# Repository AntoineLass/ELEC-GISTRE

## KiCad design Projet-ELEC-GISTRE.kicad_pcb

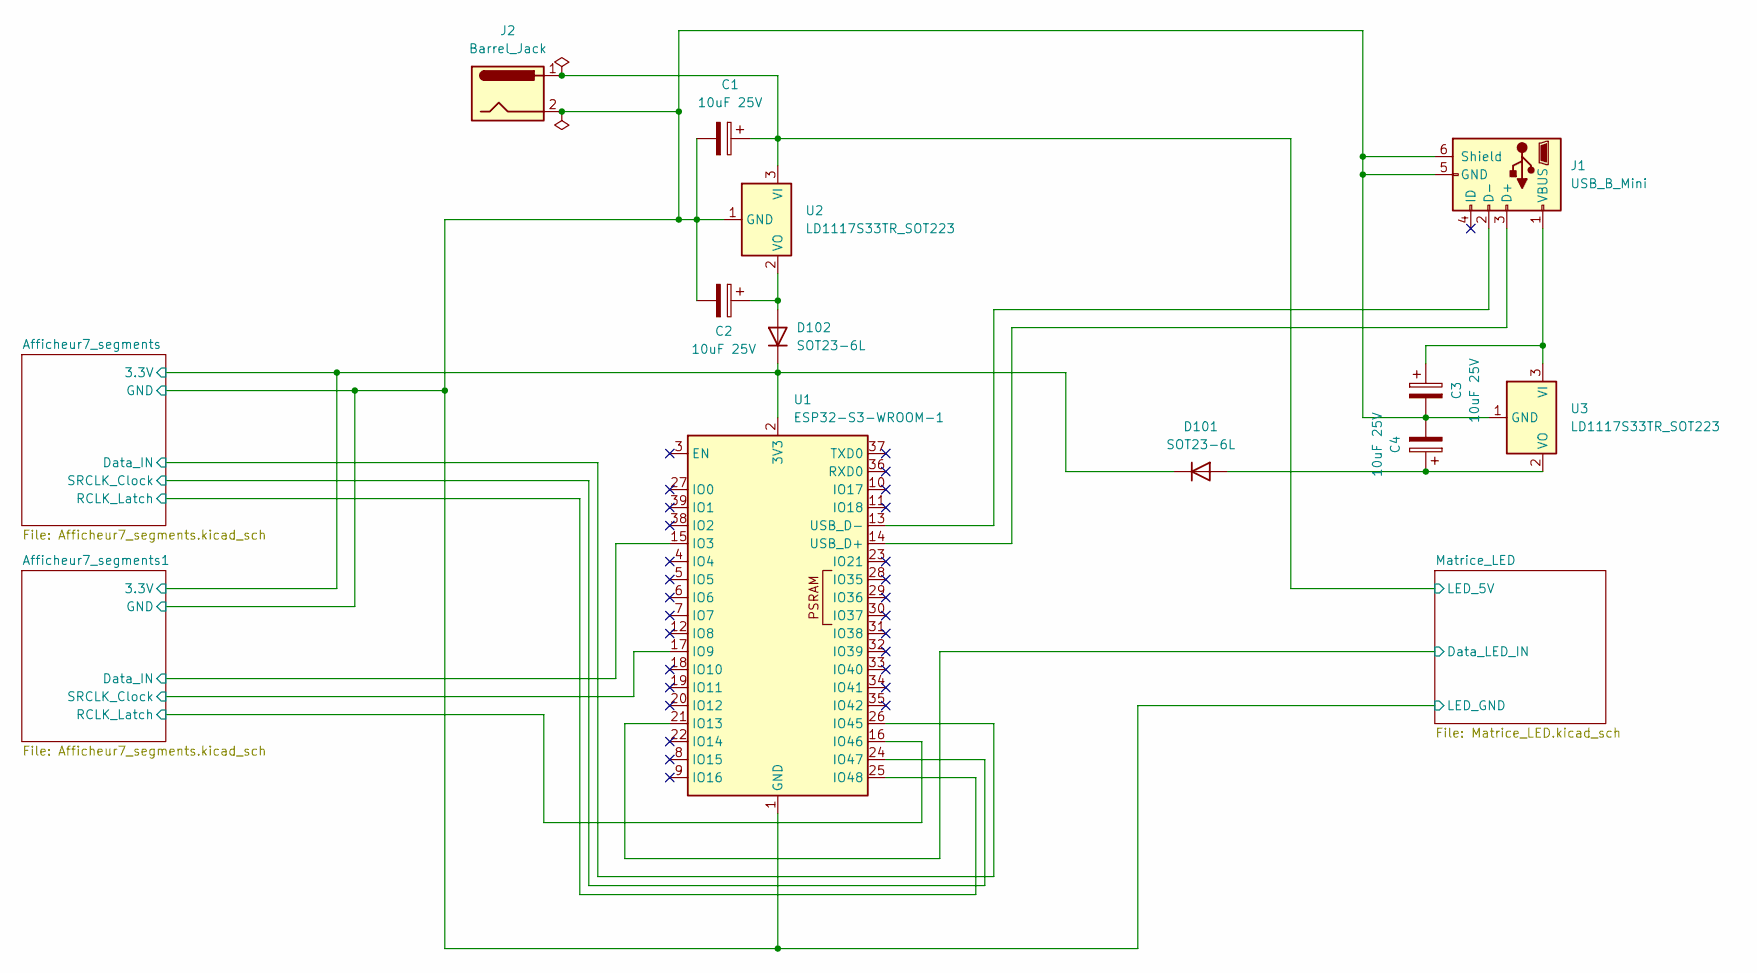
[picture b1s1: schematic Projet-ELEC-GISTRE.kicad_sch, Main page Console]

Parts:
C1, C2, C3, C4: 10uF 25V; C_0603_1608Metric_Pad1.08x0.95mm_HandSolder
D101, D102: SOT23-6L; TSOT-23-6_HandSoldering
J1: USB_B_Mini; USB_Mini-B_Wuerth_65100516121_Horizontal
J2: Barrel_Jack; BarrelJack_Wuerth_6941xx301002
U1: ESP32-S3-WROOM-1
U2, U3: LD1117S33TR_SOT223; SOT-223-3_TabPin2

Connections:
/Afficheur7_segments1/Data_IN: U1.15 (IO3); also elsewhere on the board
/Afficheur7_segments1/RCLK_Latch: U1.16 (IO46); also elsewhere on the board
/Afficheur7_segments1/SRCLK_Clock: U1.17 (IO9); also elsewhere on the board
/Afficheur7_segments/3.3V: D101.1 (K), D102.1 (K), U1.2 (3V3); also elsewhere on the board
/Afficheur7_segments/Data_IN: U1.26 (IO45); also elsewhere on the board
/Afficheur7_segments/GND: C1.2, C2.2, C3.2, C4.2, J1.5 (GND), J1.6 (Shield), J2.2, U1.1 (GND), U1.40 (GND), U1.41 (GND), U2.1 (GND), U3.1 (GND); also elsewhere on the board
/Afficheur7_segments/RCLK_Latch: U1.25 (IO48); also elsewhere on the board
/Afficheur7_segments/SRCLK_Clock: U1.24 (IO47); also elsewhere on the board
/Matrice_LED/Data_LED_IN: U1.21 (IO13); also elsewhere on the board
/Matrice_LED/LED_5V: C1.1, J2.1, U2.3 (VI); also elsewhere on the board
unnamed: C4.1, D101.2 (A), U3.2 (VO)
unnamed: C2.1, D102.2 (A), U2.2 (VO)
unnamed: J1.3 (D+), U1.14 (USB_D+)
unnamed: J1.2 (D-), U1.13 (USB_D-)
unnamed: C3.1, J1.1 (VBUS), U3.3 (VI)

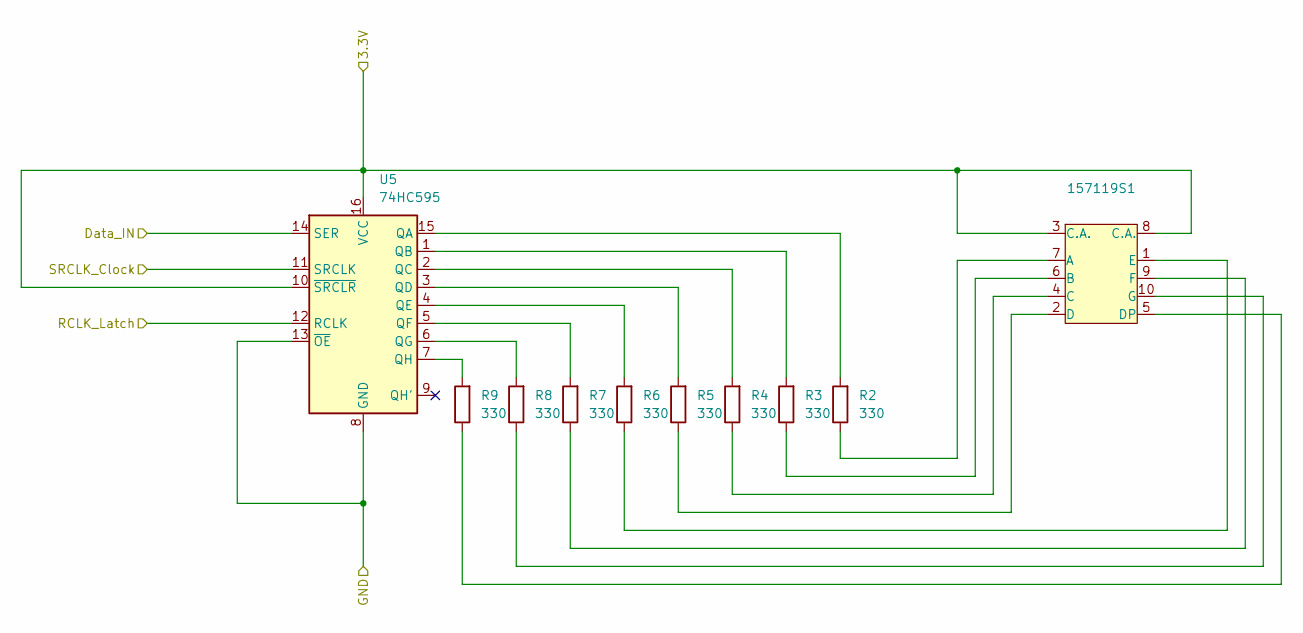
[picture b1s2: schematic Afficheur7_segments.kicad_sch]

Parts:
157119S1: 157119S12801
R2, R3, R4, R5, R6, R7, R8, R9: 330; R_0603_1608Metric_Pad0.98x0.95mm_HandSolder
U5: 74HC595; DIP-16_W7.62mm

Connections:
/Afficheur7_segments/3.3V: 157119S1.3 (C.A.), 157119S1.8 (C.A.), U5.10 (~SRCLR), U5.16 (VCC); also elsewhere on the board
/Afficheur7_segments/Data_IN: U5.14 (SER); also elsewhere on the board
/Afficheur7_segments/GND: U5.8 (GND), U5.13 (~OE); also elsewhere on the board
/Afficheur7_segments/RCLK_Latch: U5.12 (RCLK); also elsewhere on the board
/Afficheur7_segments/SRCLK_Clock: U5.11 (SRCLK); also elsewhere on the board
unnamed: 157119S1.7 (A), R2.1
unnamed: 157119S1.6 (B), R3.1
unnamed: 157119S1.4 (C), R4.1
unnamed: 157119S1.2 (D), R5.1
unnamed: 157119S1.5 (DP), R9.1
unnamed: 157119S1.1 (E), R6.1
unnamed: 157119S1.9 (F), R7.1
unnamed: 157119S1.10 (G), R8.1
unnamed: R2.2, U5.15 (QA)
unnamed: R3.2, U5.1 (QB)
unnamed: R4.2, U5.2 (QC)
unnamed: R5.2, U5.3 (QD)
unnamed: R6.2, U5.4 (QE)
unnamed: R7.2, U5.5 (QF)
unnamed: R8.2, U5.6 (QG)
unnamed: R9.2, U5.7 (QH)

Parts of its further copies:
157119S2: 157119S12801
R10, R11, R12, R13, R14, R15, R16, R17: 330; R_0603_1608Metric_Pad0.98x0.95mm_HandSolder
U4: 74HC595; DIP-16_W7.62mm

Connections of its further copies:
/Afficheur7_segments1/Data_IN: U4.14 (SER); also elsewhere on the board
/Afficheur7_segments1/RCLK_Latch: U4.12 (RCLK); also elsewhere on the board
/Afficheur7_segments1/SRCLK_Clock: U4.11 (SRCLK); also elsewhere on the board
/Afficheur7_segments/3.3V: 157119S2.3 (C.A.), 157119S2.8 (C.A.), U4.10 (~SRCLR), U4.16 (VCC); also elsewhere on the board
/Afficheur7_segments/GND: U4.8 (GND), U4.13 (~OE); also elsewhere on the board
unnamed: 157119S2.7 (A), R17.1
unnamed: 157119S2.6 (B), R16.1
unnamed: 157119S2.4 (C), R15.1
unnamed: 157119S2.2 (D), R14.1
unnamed: 157119S2.5 (DP), R10.1
unnamed: 157119S2.1 (E), R13.1
unnamed: 157119S2.9 (F), R12.1
unnamed: 157119S2.10 (G), R11.1
unnamed: R17.2, U4.15 (QA)
unnamed: R16.2, U4.1 (QB)
unnamed: R15.2, U4.2 (QC)
unnamed: R14.2, U4.3 (QD)
unnamed: R13.2, U4.4 (QE)
unnamed: R12.2, U4.5 (QF)
unnamed: R11.2, U4.6 (QG)
unnamed: R10.2, U4.7 (QH)

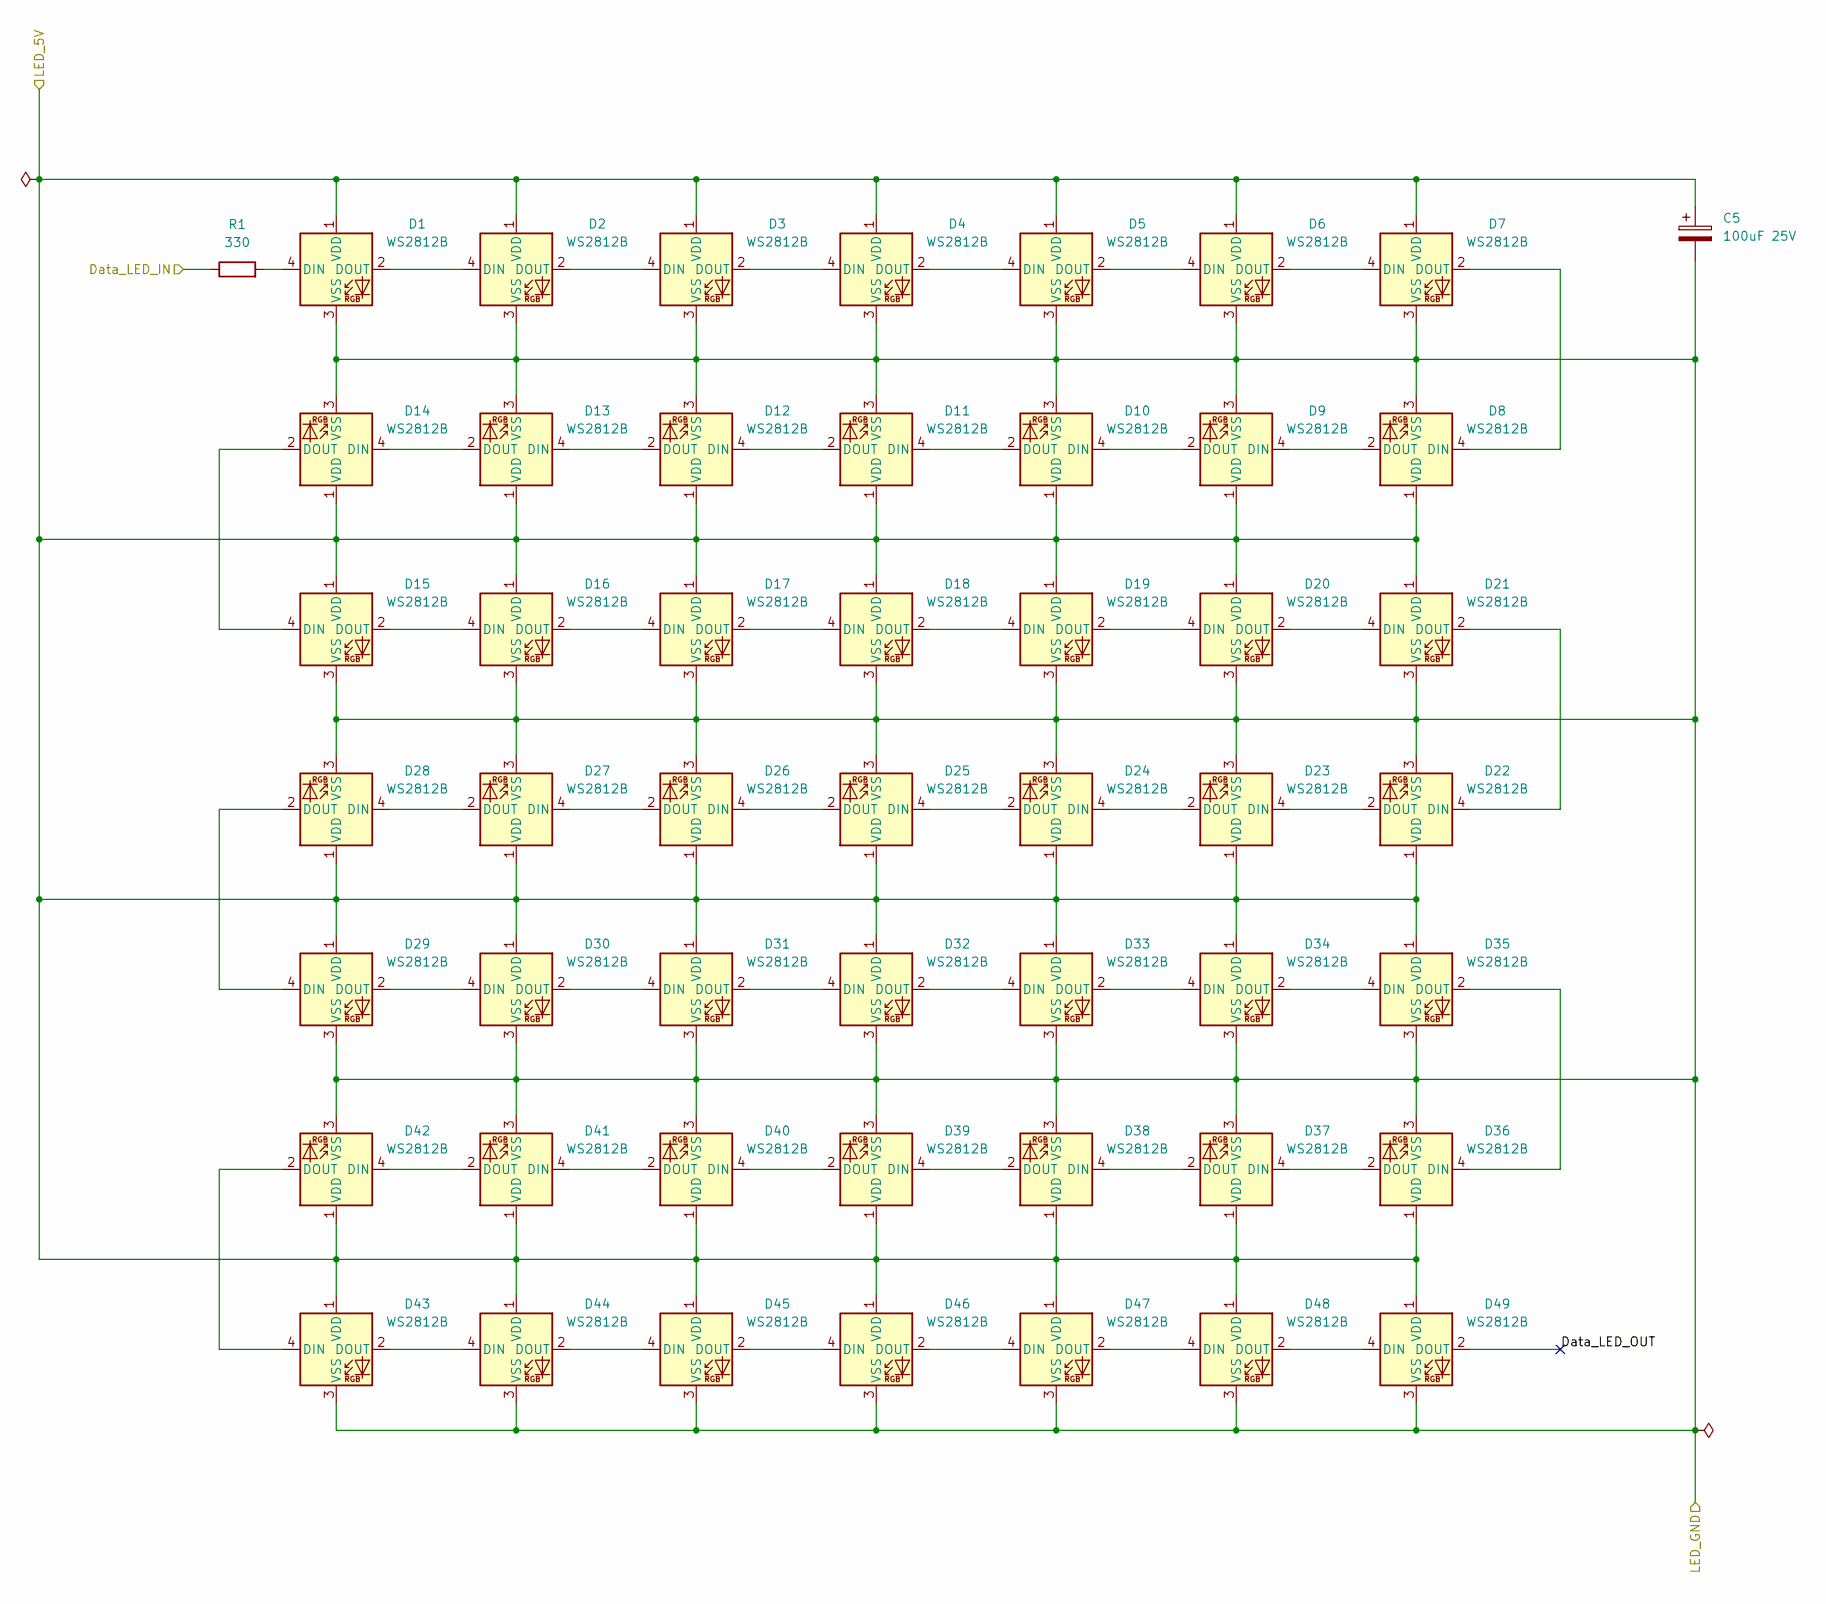
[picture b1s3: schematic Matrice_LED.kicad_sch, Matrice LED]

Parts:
C5: 100uF 25V; CP_Elec_6.3x7.7
D1, D2, D3, D4, D5, D6, D7, D8, D9, D10, D11, D12, D13, D14, D15, D16, D17, D18, D19, D20, D21, D22, D23, D24, D25, D26, D27, D28, D29, D30, D31, D32, D33, D34, D35, D36, D37, D38, D39, D40, D41, D42, D43, D44, D45, D46, D47, D48, D49: WS2812B; LED_WS2812B_PLCC4_5.0x5.0mm_P3.2mm
R1: 330; R_0603_1608Metric_Pad0.98x0.95mm_HandSolder

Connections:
/Afficheur7_segments/GND: C5.2, D1.3 (VSS), D2.3 (VSS), D3.3 (VSS), D4.3 (VSS), D5.3 (VSS), D6.3 (VSS), D7.3 (VSS), D8.3 (VSS), D9.3 (VSS), D10.3 (VSS), D11.3 (VSS), D12.3 (VSS), D13.3 (VSS), D14.3 (VSS), D15.3 (VSS), D16.3 (VSS), D17.3 (VSS), D18.3 (VSS), D19.3 (VSS), D20.3 (VSS), D21.3 (VSS), D22.3 (VSS), D23.3 (VSS), D24.3 (VSS), D25.3 (VSS), D26.3 (VSS), D27.3 (VSS), D28.3 (VSS), D29.3 (VSS), D30.3 (VSS), D31.3 (VSS), D32.3 (VSS), D33.3 (VSS), D34.3 (VSS), D35.3 (VSS), D36.3 (VSS), D37.3 (VSS), D38.3 (VSS), D39.3 (VSS), D40.3 (VSS), D41.3 (VSS), D42.3 (VSS), D43.3 (VSS), D44.3 (VSS), D45.3 (VSS), D46.3 (VSS), D47.3 (VSS), D48.3 (VSS), D49.3 (VSS); also elsewhere on the board
/Matrice_LED/Data_LED_IN: R1.1; also elsewhere on the board
/Matrice_LED/Data_LED_OUT: D49.2 (DOUT)
/Matrice_LED/LED_5V: C5.1, D1.1 (VDD), D2.1 (VDD), D3.1 (VDD), D4.1 (VDD), D5.1 (VDD), D6.1 (VDD), D7.1 (VDD), D8.1 (VDD), D9.1 (VDD), D10.1 (VDD), D11.1 (VDD), D12.1 (VDD), D13.1 (VDD), D14.1 (VDD), D15.1 (VDD), D16.1 (VDD), D17.1 (VDD), D18.1 (VDD), D19.1 (VDD), D20.1 (VDD), D21.1 (VDD), D22.1 (VDD), D23.1 (VDD), D24.1 (VDD), D25.1 (VDD), D26.1 (VDD), D27.1 (VDD), D28.1 (VDD), D29.1 (VDD), D30.1 (VDD), D31.1 (VDD), D32.1 (VDD), D33.1 (VDD), D34.1 (VDD), D35.1 (VDD), D36.1 (VDD), D37.1 (VDD), D38.1 (VDD), D39.1 (VDD), D40.1 (VDD), D41.1 (VDD), D42.1 (VDD), D43.1 (VDD), D44.1 (VDD), D45.1 (VDD), D46.1 (VDD), D47.1 (VDD), D48.1 (VDD), D49.1 (VDD); also elsewhere on the board
unnamed: D1.4 (DIN), R1.2
unnamed: D1.2 (DOUT), D2.4 (DIN)
unnamed: D2.2 (DOUT), D3.4 (DIN)
unnamed: D3.2 (DOUT), D4.4 (DIN)
unnamed: D4.2 (DOUT), D5.4 (DIN)
unnamed: D5.2 (DOUT), D6.4 (DIN)
unnamed: D6.2 (DOUT), D7.4 (DIN)
unnamed: D7.2 (DOUT), D8.4 (DIN)
unnamed: D8.2 (DOUT), D9.4 (DIN)
unnamed: D9.2 (DOUT), D10.4 (DIN)
unnamed: D10.2 (DOUT), D11.4 (DIN)
unnamed: D11.2 (DOUT), D12.4 (DIN)
unnamed: D12.2 (DOUT), D13.4 (DIN)
unnamed: D13.2 (DOUT), D14.4 (DIN)
unnamed: D14.2 (DOUT), D15.4 (DIN)
unnamed: D15.2 (DOUT), D16.4 (DIN)
unnamed: D16.2 (DOUT), D17.4 (DIN)
unnamed: D17.2 (DOUT), D18.4 (DIN)
unnamed: D18.2 (DOUT), D19.4 (DIN)
unnamed: D19.2 (DOUT), D20.4 (DIN)
unnamed: D20.2 (DOUT), D21.4 (DIN)
unnamed: D21.2 (DOUT), D22.4 (DIN)
unnamed: D22.2 (DOUT), D23.4 (DIN)
unnamed: D23.2 (DOUT), D24.4 (DIN)
unnamed: D24.2 (DOUT), D25.4 (DIN)
unnamed: D25.2 (DOUT), D26.4 (DIN)
unnamed: D26.2 (DOUT), D27.4 (DIN)
unnamed: D27.2 (DOUT), D28.4 (DIN)
unnamed: D28.2 (DOUT), D29.4 (DIN)
unnamed: D29.2 (DOUT), D30.4 (DIN)
unnamed: D30.2 (DOUT), D31.4 (DIN)
unnamed: D31.2 (DOUT), D32.4 (DIN)
unnamed: D32.2 (DOUT), D33.4 (DIN)
unnamed: D33.2 (DOUT), D34.4 (DIN)
unnamed: D34.2 (DOUT), D35.4 (DIN)
unnamed: D35.2 (DOUT), D36.4 (DIN)
unnamed: D36.2 (DOUT), D37.4 (DIN)
unnamed: D37.2 (DOUT), D38.4 (DIN)
unnamed: D38.2 (DOUT), D39.4 (DIN)
unnamed: D39.2 (DOUT), D40.4 (DIN)
unnamed: D40.2 (DOUT), D41.4 (DIN)
unnamed: D41.2 (DOUT), D42.4 (DIN)
unnamed: D42.2 (DOUT), D43.4 (DIN)
unnamed: D43.2 (DOUT), D44.4 (DIN)
unnamed: D44.2 (DOUT), D45.4 (DIN)
unnamed: D45.2 (DOUT), D46.4 (DIN)
unnamed: D46.2 (DOUT), D47.4 (DIN)
unnamed: D47.2 (DOUT), D48.4 (DIN)
unnamed: D48.2 (DOUT), D49.4 (DIN)

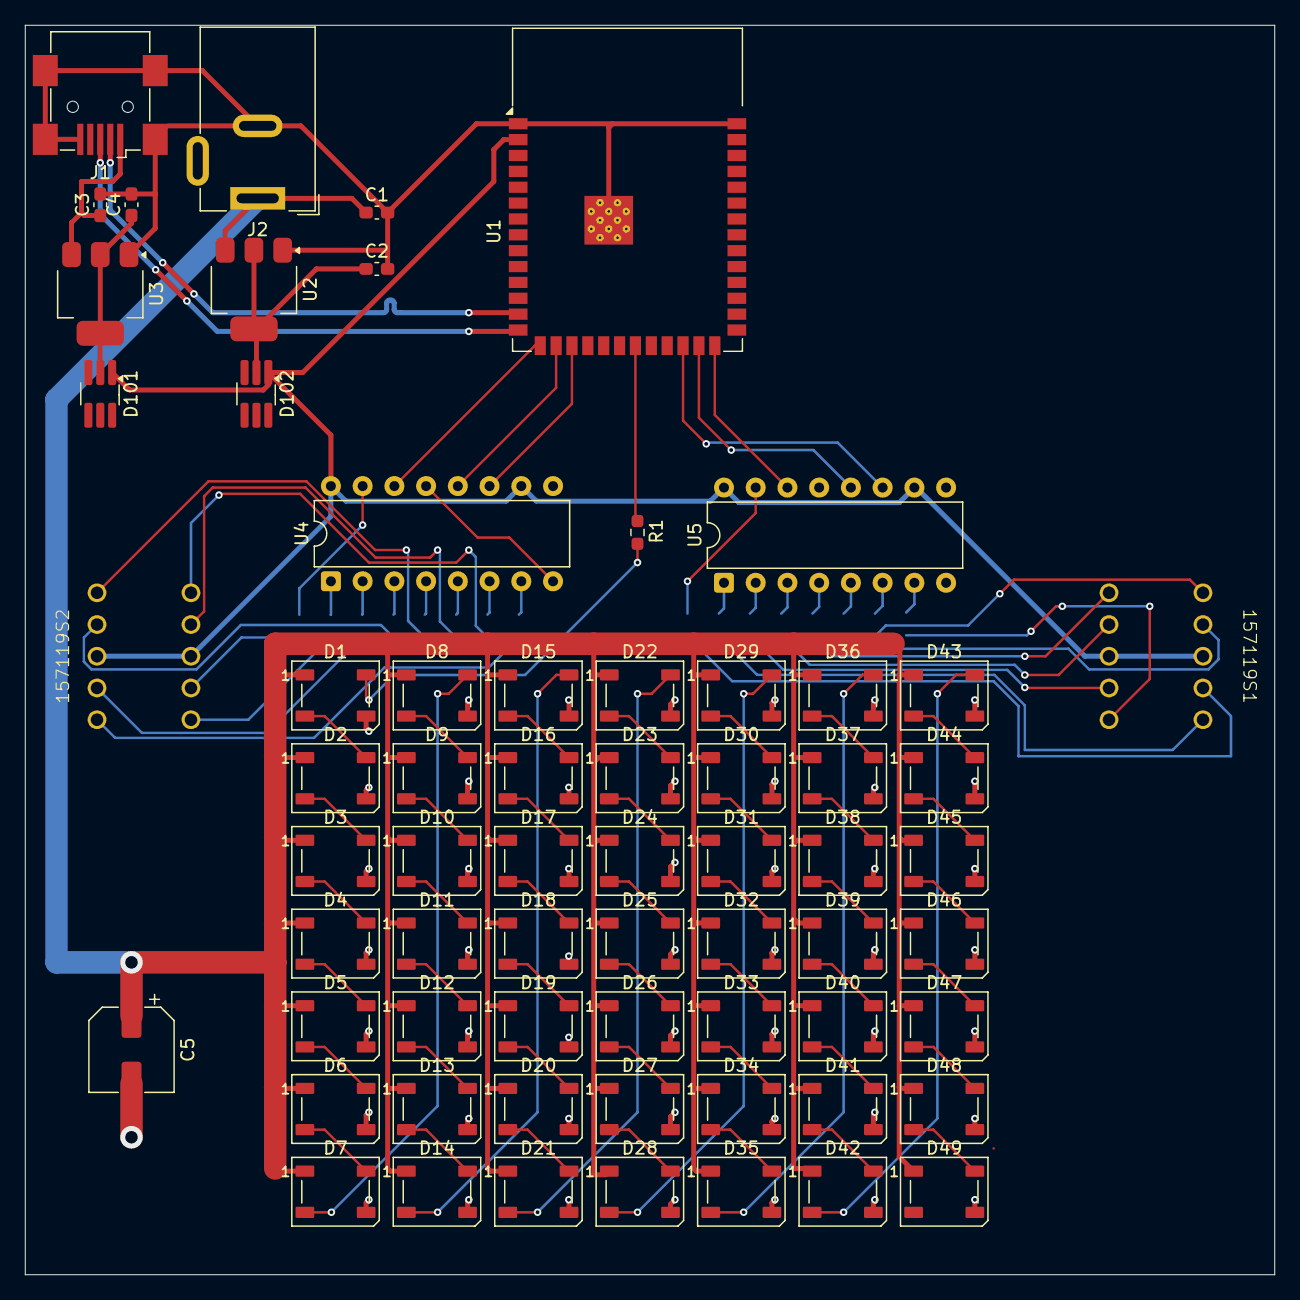
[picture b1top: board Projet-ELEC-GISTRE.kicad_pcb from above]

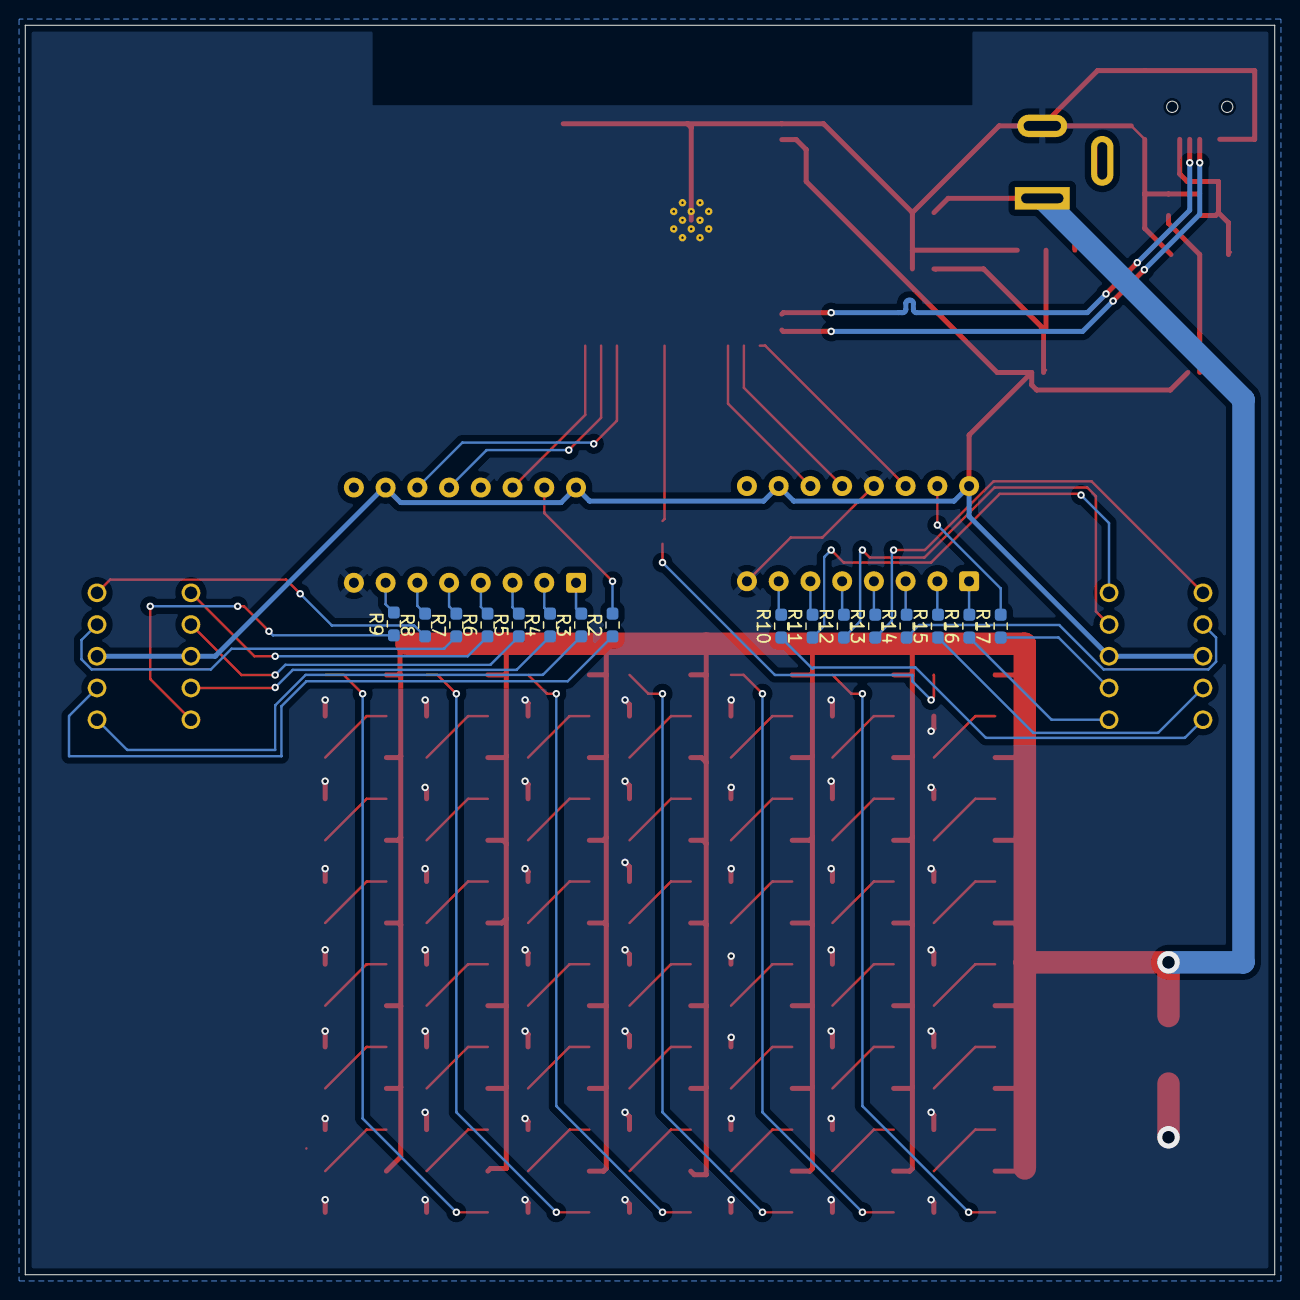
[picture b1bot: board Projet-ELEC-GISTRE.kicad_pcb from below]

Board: 2 copper layers, 100.0 x 100.0 mm, 82 parts (16 on the bottom side), 96 nets.

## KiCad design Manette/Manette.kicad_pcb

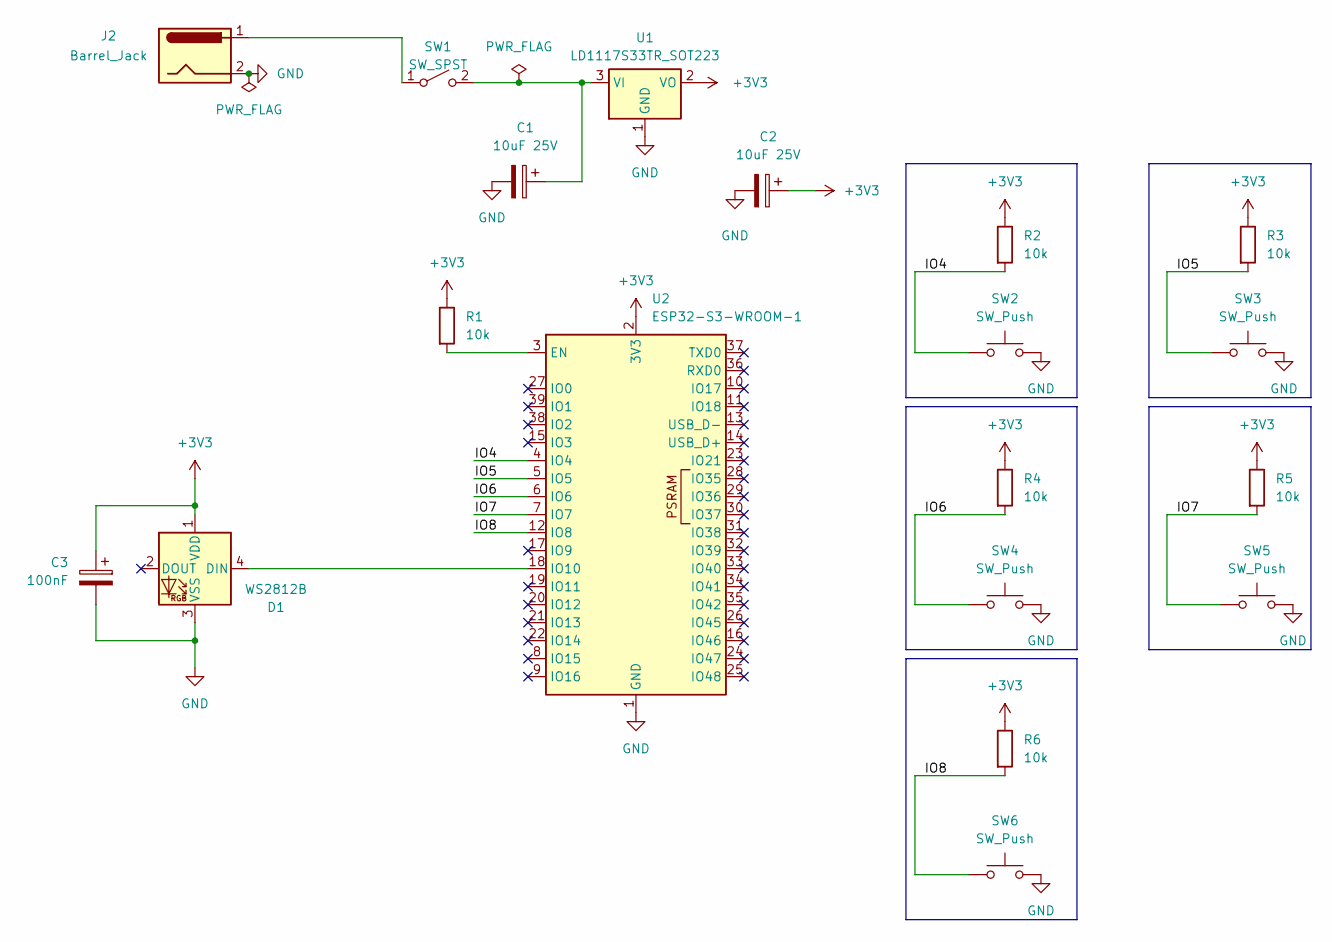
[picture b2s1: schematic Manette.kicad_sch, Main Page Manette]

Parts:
C1, C2: 10uF 25V
C3: 100nF
D1: WS2812B; LED_WS2812B_PLCC4_5.0x5.0mm_P3.2mm
J2: Barrel_Jack
R1, R2, R3, R4, R5, R6: 10k
SW1: SW_SPST
SW2, SW3, SW4, SW5, SW6: SW_Push
U1: LD1117S33TR_SOT223; SOT-223-3_TabPin2
U2: ESP32-S3-WROOM-1

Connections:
+3V3: C2.1, C3.1, D1.1 (VDD), R1.1, R2.1, R3.1, R4.1, R5.1, R6.1, U1.2 (VO), U2.2 (3V3)
/IO4: R2.2, SW2.1, U2.4 (IO4)
/IO5: R3.2, SW3.1, U2.5 (IO5)
/IO6: R4.2, SW4.1, U2.6 (IO6)
/IO7: R5.2, SW5.1, U2.7 (IO7)
/IO8: R6.2, SW6.1, U2.12 (IO8)
GND: C1.2, C2.2, C3.2, D1.3 (VSS), J2.2, SW2.2, SW3.2, SW4.2, SW5.2, SW6.2, U1.1 (GND), U2.1 (GND), U2.40 (GND), U2.41 (GND); also elsewhere on the board
unnamed: D1.4 (DIN), U2.18 (IO10)
unnamed 8: J2.1, SW1.1 (A); also elsewhere on the board
unnamed: C1.1, SW1.2 (B), U1.3 (VI)
unnamed: R1.2, U2.3 (EN)

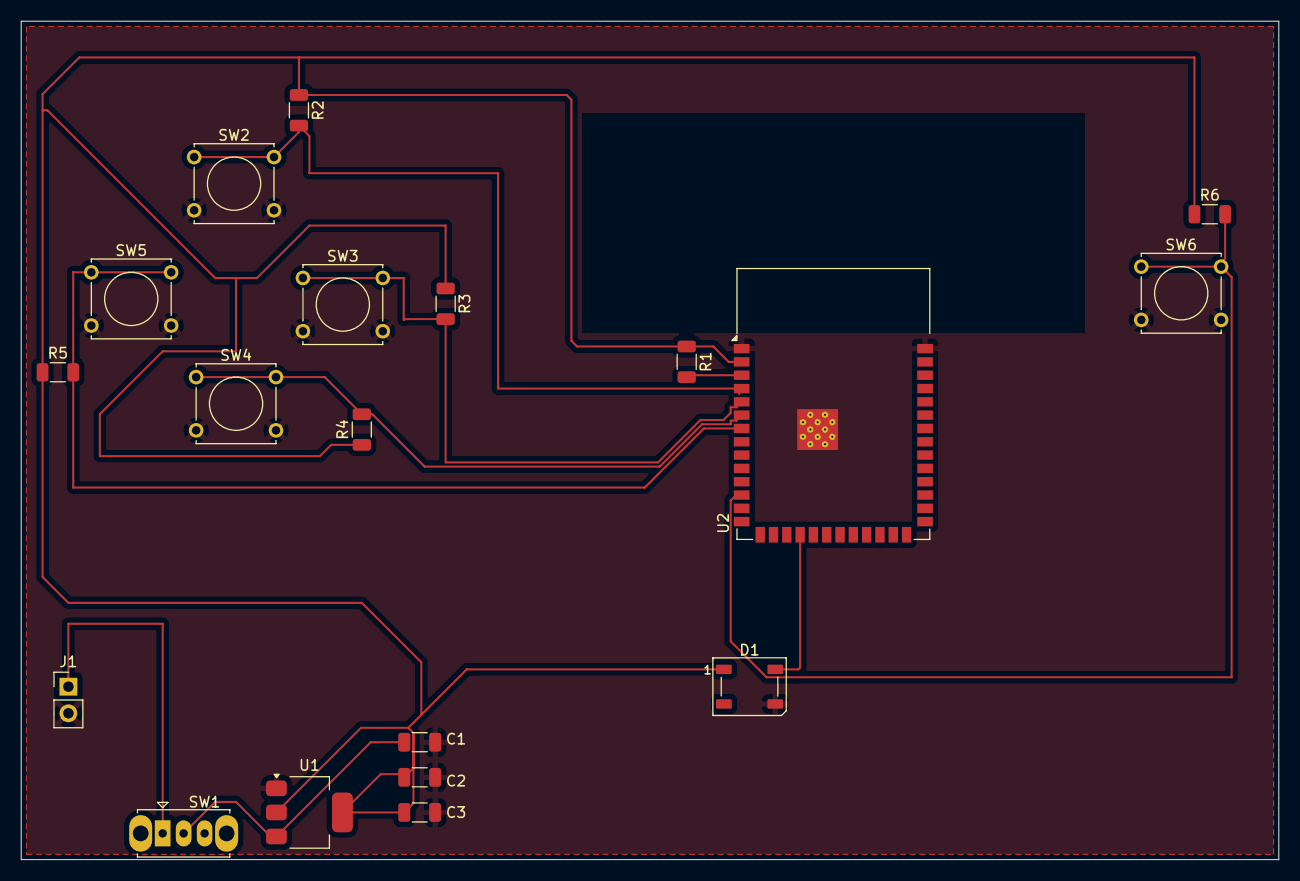
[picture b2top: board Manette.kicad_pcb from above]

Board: 2 copper layers, 120.0 x 80.0 mm, 19 parts (0 on the bottom side), 11 nets.

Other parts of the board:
J1: Conn_01x02_Pin; PinHeader_1x02_P2.54mm_Vertical

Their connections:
GND: J1.2; also elsewhere on the board
unnamed 8: J1.1; also elsewhere on the board

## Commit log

2026-03-11 Project init: matrix of led and 7 seg display are already here
2026-03-17 Add the barel and the usb to transfer code to esp32
2026-03-28 feat(manette): add the game controller kicad schematic
2026-03-30 feat(manette): add the pcb design for the game controller
2026-03-30 fix(manette): removed the barrel jack with a 2 pin connector to place the 4 battery holder
2026-03-30 Save for the review
